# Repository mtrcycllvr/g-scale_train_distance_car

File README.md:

## Data Car

Something of a mess and untested repository of files related to me wanting to build a 'better' track distance car and realized that people are ALSO interested in a scale speedometer that they can see from a distance..  That's where this high sample rate design has the advantage over other two to four magnet per wheel designs.

We can wick the encoder up to max res and find ourselves with 8k pulses (directional via quadrature) per wheel revolution..  INSTANT accurate low speed speedometer calcs.  Well, quickly..

# g-scale_train_distance_car <br>
Use CUI encoder and teensy to create "track distance car" <br>
Description	Quantity	Unit Price	Cost <br>
AMT102-V	      1	      $23.63	$23.63 <br>
CUI-3132-1FT	  1	          $6	$6 <br>
Teensy 3.2 with headers	1	$19.5	$19.5 <br>
2.8” TFT LCD touch screen	1	$15	$15 <br>
Purple “Test Board”	1	      $5	$5 <br>
Power Boost 500C	1	      $14.95	$14.95 <br>
Lithium Battery	1	          $9.95	$9.95 <br>
power switch	1	            $1	$1 <br>
5 position dupont connector housing w/pins	1	$1	$1 <br>
battery mount	1	            $1	$1 <br>
beeper 668-1470-ND	1	      $0.6	$0.6 <br>
Label, headers, misc 1	    $10	$10 <br>
		              Subtotal	$107.63 <br>

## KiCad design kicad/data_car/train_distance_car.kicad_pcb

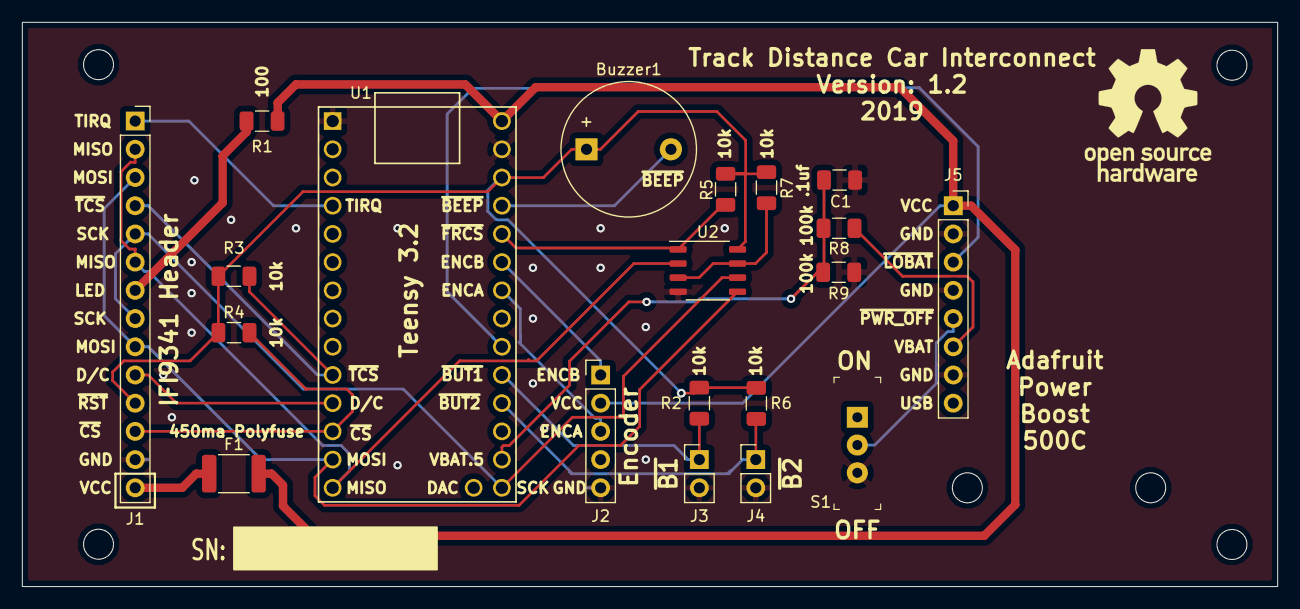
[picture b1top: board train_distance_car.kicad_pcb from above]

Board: 2 copper layers, 113.0 x 50.8 mm, 27 parts (1 on the bottom side), 23 nets.

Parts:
Buzzer1: Buzzer; Buzzer_12x9.5RM7.6
C1: .1uf; C_1206_3216Metric
F1: 450mA Polyfuse; Fuse_1812_4532Metric_Pad1.30x3.40mm_HandSolder
H1, H2, H3, H4, H5, H6: hole; MountingHole_2.7mm_M2.5
J1: IFI9431 Header; PinSocket_1x14_P2.54mm_Vertical
J2: Encoder Header; PinHeader_1x05_P2.54mm_Vertical
J3, J4: Button Header; PinHeader_1x02_P2.54mm_Vertical
J5: Adafruit 500C Header; PinSocket_1x08_P2.54mm_Vertical
R1: 100; R_1206_3216Metric
R2, R3, R4, R5, R6, R7: 10k; R_1206_3216Metric
R8, R9: 100k; R_1206_3216Metric
RCGRS_sm: RCGRS_sm
S1: EG1218; Switch_Slide_11.6x4mm_EG1218
U1: Teensy3.2; Teensy30_31_32_LC_audio_only
U2: MB85RS16; SSOP-8_3.9x5.05mm_P1.27mm

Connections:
+3V3: Buzzer1.1, J1.11, R2.1, R3.1, R4.1, R5.1, R6.1, R7.1, U1.31, U2.8
+5V: F1.2, J2.2, J5.1, R1.1, U1.33
DnC: J1.10, U1.11
ENC-A: J2.3, U1.27
ENC-B: J2.1, U1.28
GND: C1.2, J1.13, J2.5, J3.2, J4.2, J5.2, J5.4, J5.7, R9.2, S1.3, U1.1, U1.32, U2.4
MISO: J1.2, J1.6, U1.14, U2.2
MOSI: J1.3, J1.9, U1.13, U2.5
unnamed: Buzzer1.2, U1.30
unnamed: F1.1, J1.14
unnamed: J1.7, R1.2
unnamed: R7.2, U2.3, U2.7
SCK: J1.5, J1.8, U1.20, U2.6
TIRQ: J1.1, U1.4
VBAT: J5.6, R8.1
VBAT.5: C1.1, R8.2, R9.1, U1.21
~BUTTON1: J3.1, R2.2, U1.24
~BUTTON2: J4.1, R6.2, U1.23
~CS: J1.12, R4.2, U1.12
~FRCS: R5.2, U1.29, U2.1
~LOBAT: J5.3, U1.25
~PWR_OFF: J5.5, S1.2
~TCS: J1.4, R3.2, U1.10

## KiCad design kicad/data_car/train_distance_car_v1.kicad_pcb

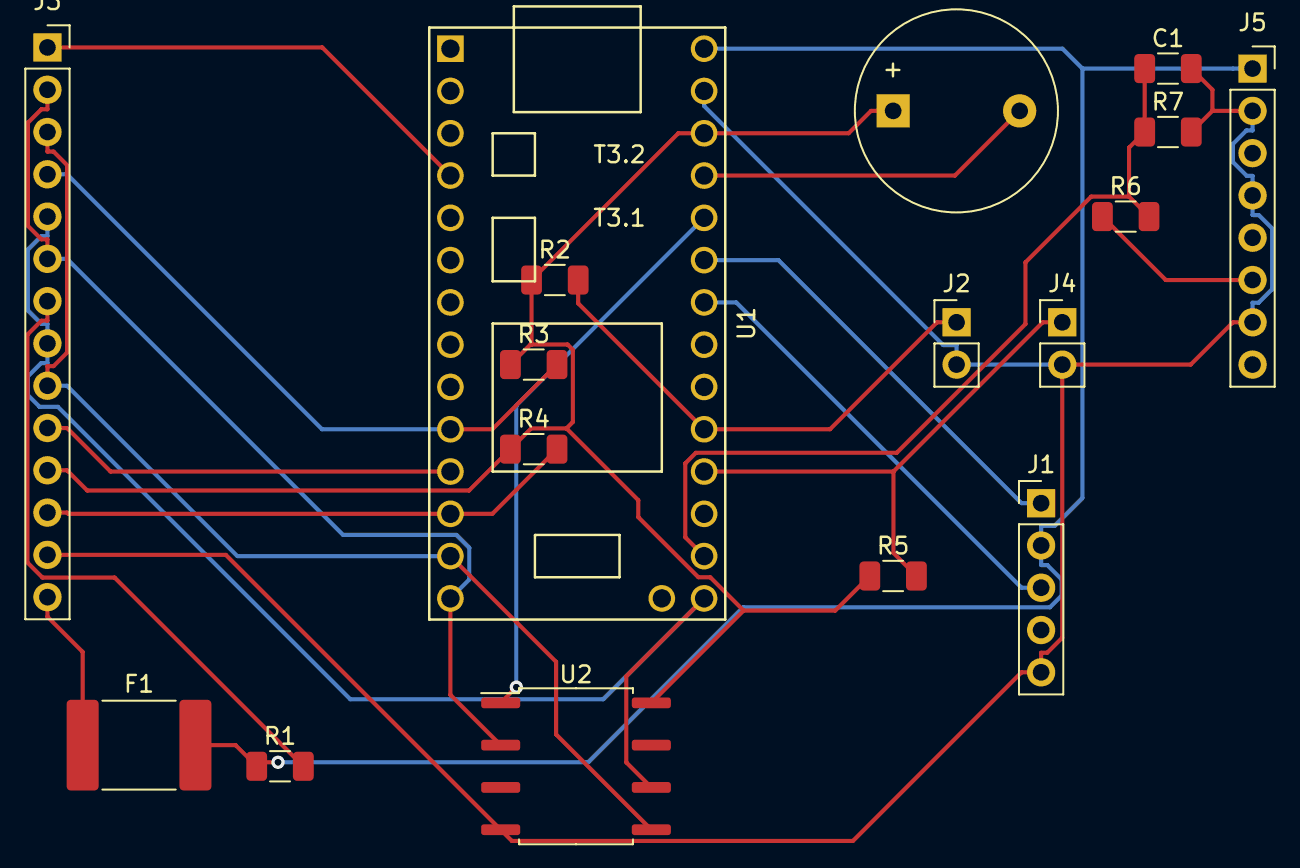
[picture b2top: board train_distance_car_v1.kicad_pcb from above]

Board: 2 copper layers, 17 parts (0 on the bottom side), 20 nets.

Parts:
BZ1: Buzzer; Buzzer_12x9.5RM7.6
C1: .1uf; C_1206_3216Metric
F1: 450mA Polyfuse; Fuse_2920_7451Metric
J1: Encoder Header; PinHeader_1x05_P2.54mm_Vertical
J2, J4: Button Header; PinHeader_1x02_P2.54mm_Vertical
J3: IFI9431 Header; PinSocket_1x14_P2.54mm_Vertical
J5: Adafruit 500C Header; PinSocket_1x08_P2.54mm_Vertical
R1: 100; R_1206_3216Metric
R2, R3, R4, R5: 10k; R_1206_3216Metric
R6, R7: 100k; R_1206_3216Metric
U1: Teensy3.2; Teensy30_31_32_LC_audio_only
U2: MB85RS16; SOP-8_6.62x9.15mm_P2.54mm

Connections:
+3V3: BZ1.1, J3.11, R2.1, R3.1, R4.1, R5.1, U1.31, U2.8
+5V: F1.2, J1.2, J5.1, R1.1, U1.33
CS: J3.12, R4.2, U1.12
DnC: J3.10, U1.11
ENC-A: J1.3, U1.27
ENC-B: J1.1, U1.28
GND: C1.2, J1.5, J2.2, J3.13, J4.2, J5.2, J5.4, J5.7, R7.2, U1.32, U2.4
MISO: J3.2, J3.6, U1.14, U2.2
MOSI: J3.3, J3.9, U1.13, U2.5
unnamed: BZ1.2, U1.30
unnamed: F1.1, J3.14
unnamed: J3.7, R1.2
SCK: J3.5, J3.8, U1.20, U2.6
TCS: J3.4, R3.2, U1.10
TIRQ: J3.1, U1.4
VBAT: J5.6, R6.1
VBAT.5: C1.1, R6.2, R7.1, U1.21
~BUTTON1: J2.1, R2.2, U1.24
~BUTTON2: J4.1, R5.2, U1.23
~FRCS: U1.29, U2.1

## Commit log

2019-02-25 Add files via upload
    KiCad interconnect schematic and board layout - version 1.0
2019-02-25 updating structure
2019-02-25 added assets
2019-02-25 Update README.md
    add photo?
2019-02-26 added new RA adapters
2019-03-23 Update to version 1.2 PCB - fixed parts profiles. Changes to be committed: deleted: kicad/data_car/sym-lib-table deleted: kicad/data_car/train_distance_car-cache.lib deleted: kicad/data_car/train_dis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

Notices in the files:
kicad/data_car/train_distance_car.kicad_pcb:
License: CC BY 4.0
